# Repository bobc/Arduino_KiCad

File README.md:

# Arduino projects converted to KiCad

This repository contains Eagle projects that have been automatically converted to KiCad (v4) format  by eakit.

The conversion is as far as possible identical to the original, but some features of Eagle cannot be converted directly to KiCad. 

They may (probably will) contain conversion errors - use at own risk!

If you find a conversion problem, please raise an issue here. In case of doubt, the Eagle project should be preferred. 

If you find a problem with the design of a project, or wish to make a feature request,
please do not raise an issue here, contact the original designers.

## Copyright

Copyrights and license terms for each project are as specified by original author(s). 

## Trademarks

Please respect trademarks where applicable, and do not use without permission. 

- "Arduino", "Genuino", and the Arduino logo are trademarks of Arduino AG. https://www.arduino.cc/en/Main/CopyrightNotice

## eakit

eakit project: https://github.com/bobc/eakit

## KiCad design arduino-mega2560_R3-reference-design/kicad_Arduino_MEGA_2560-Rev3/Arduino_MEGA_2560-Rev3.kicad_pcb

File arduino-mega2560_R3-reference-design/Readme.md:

# Project automatically converted by eakit

This project was automatically converted by eakit to KiCad format.

It may (probably will) contain conversion errors - use at own risk!

eakit project: https://github.com/bobc/eakit

## Source of project

https://www.arduino.cc/en/Main/ArduinoBoardMega2560 retrieved on 2017-04-15

## License

https://www.arduino.cc/en/Main/FAQ retrieved on 2017-04-15              

> These files are licensed under a Creative Commons Attribution Share-Alike license, which allows for both personal and commercial derivative works, as long as they credit Arduino and release their designs under the same license.

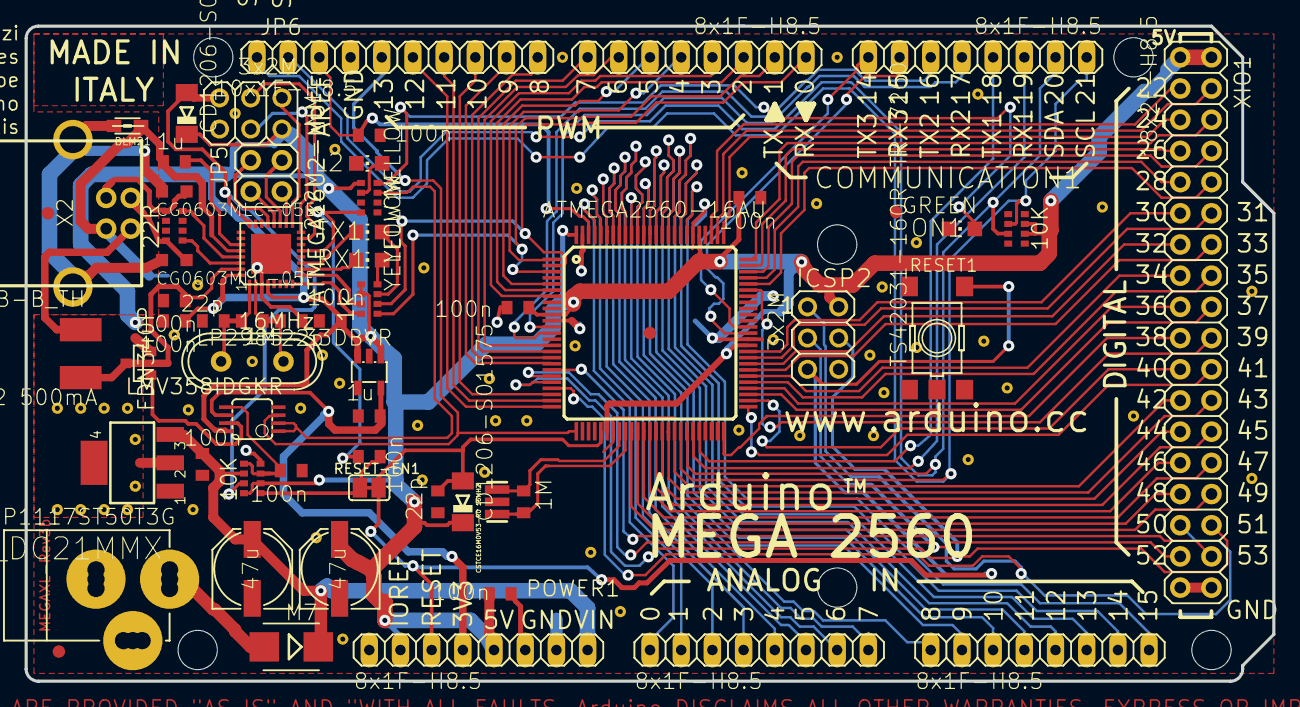
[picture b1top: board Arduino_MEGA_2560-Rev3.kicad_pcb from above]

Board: 2 copper layers, 101.6 x 53.3 mm, 123 parts (0 on the bottom side), 110 nets.

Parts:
@HOLE1: @HOLE1
@HOLE2: @HOLE2
@HOLE3: @HOLE3
@HOLE4: @HOLE4
@HOLE5: @HOLE5
@HOLE6: @HOLE6
@V1: @V1
@V2: @V2
@V3: @V3
@V4: @V4
@V5: @V5
@V6: @V6
@V7: @V7
@V8: @V8
@V9: @V9
@V10: @V10
@V11: @V11
@V12: @V12
@V13: @V13
@V14: @V14
@V15: @V15
@V16: @V16
@V17: @V17
@V18: @V18
@V19: @V19
@V20: @V20
@V21: @V21
@V22: @V22
@V23: @V23
@V24: @V24
@V25: @V25
@V26: @V26
@V27: @V27
@V28: @V28
@V29: @V29
@V30: @V30
@V31: @V31
@V32: @V32
@V33: @V33
@V34: @V34
@V35: @V35
@V36: @V36
@V37: @V37
@V38: @V38
@V39: @V39
@V40: @V40
@V41: @V41
@V42: @V42
@V43: @V43
@V44: @V44
@V45: @V45
@V46: @V46
@V47: @V47
@V48: @V48
@V49: @V49
@V50: @V50
@V51: @V51
@V52: @V52
@V53: @V53
@V54: @V54
ADCH1: 8x1F-H8.5; 1X08
ADCL1: 8x1F-H8.5; 1X08
C1, C14, C15: 22p; C0603-ROUND
C2, C3, C4, C5, C6, C7, C8, C9, C11, C12: 100n; C0603-ROUND
C10, C13: 1u; C0603-ROUND
COMMUNICATION1: 8x1F-H8.5; 1X08
D1: M7; SMB
D2, D3: CD1206-S01575; MINIMELF
F1: MF-MSMF050-2 500mA; L1812
FD1, FD2, FD3, FD4: FIDUCIALMOUNT; FIDUCIA-MOUNT
GROUND1: SJ
IC1: NCP1117ST50T3G; SOT223
IC3: ATMEGA2560-16AU; TQFP100
IC4: ATMEGA16U2-MU; MLF32
IC6: LP2985-33DBVR; SOT23-DBV
IC7: LMV358IDGKR; MSOP08
ICSP1, ICSP2: 3x2M; 2X03
JP5: 2x2M - NM; 2X02
JP6: 10x1F-H8.5; 1X10
L1: BLM21; 0805
L2: YELLOW; CHIP-LED0805
ON1: GREEN; CHIP-LED0805
PC1, PC2: 47u; PANASONIC_D
POWER1: 8x1F-H8.5; 1X08
PWML1: 8x1F-H8.5; 1X08
R1, R2: 1M; R0603-ROUND
RESET1: TS42031-160R-TR-7260; TS42
RESET-EN1: SJ
RN1, RN5: 10K; CAT16
RN2: 22R; CAY16
RN3, RN4: 1k; CAY16
RX1: YELLOW; CHIP-LED0805
T1: FDN340P; SOT-23
TX1: YELLOW; CHIP-LED0805
U$1: DISCLAIMER
X1: POWERSUPPLY_DC21MMX; POWERSUPPLY_DC-21MM
X2: USB-B_TH; PN61729
XIO1: 18x2F-H8.5; 2X18
Y1: CSTCE16M0V53-R0 16MHZ; RESONATOR
Y2: 16MHz; QS
Z1, Z2: CG0603MLC-05E; CT_CN0603

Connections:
8PB4: IC4.18, JP5.1
8PB5: IC4.19, JP5.3
8PB6: IC4.20, JP5.2
8PB7: IC4.21, JP5.4
+3V3: C13.2, IC6.5, IC7.6, POWER1.4
+5V: C4.1, C5.1, C6.1, C9.1, C11.2, D2.C, D3.C, IC1.2, IC1.4, IC3.10, IC3.31, IC3.61, IC3.80, IC3.100, IC4.4, IC4.32, IC6.1, IC6.3, IC7.8, ICSP1.2, ICSP2.2, PC2.+, POWER1.2, POWER1.5, RN1.6, RN1.7, RN3.1, RN4.5, RN4.6, RN5.2, RN5.8, T1.2, XIO1.1, XIO1.2
ADC0: ADCL1.1, IC3.97
ADC1: ADCL1.2, IC3.96
ADC2: ADCL1.3, IC3.95
ADC3: ADCL1.4, IC3.94
ADC4: ADCL1.5, IC3.93
ADC5: ADCL1.6, IC3.92
ADC6: ADCL1.7, IC3.91
ADC7: ADCL1.8, IC3.90
ADC8: ADCH1.1, IC3.89
ADC9: ADCH1.2, IC3.88
ADC10: ADCH1.3, IC3.87
ADC11: ADCH1.4, IC3.86
ADC12: ADCH1.5, IC3.85
ADC13: ADCH1.6, IC3.84
ADC14: ADCH1.7, IC3.83
ADC15: ADCH1.8, IC3.82
AREF: C3.1, IC3.98, JP6.3
CMP: C12.2, IC7.5, RN5.3, RN5.5
D+: RN2.5, X2.3, Z2.2
D-: RN2.8, X2.2, Z1.2
DTR: C7.1, IC4.13, RN3.4
GATE_CMD: IC7.7, T1.3
GND: C1.2, C2.2, C3.2, C4.2, C5.2, C6.2, C8.2, C9.2, C11.1, C12.1, C13.1, C14.2, C15.2, GROUND1.2, IC1.1, IC3.11, IC3.32, IC3.62, IC3.81, IC3.99, IC4.3, IC4.33, IC6.2, IC7.4, ICSP1.6, ICSP2.6, JP6.4, L2.C, ON1.C, PC1.-, PC2.-, POWER1.6, POWER1.7, RESET1.1, RESET1.2, RN3.5, RN5.4, X1.1, X1.3, XIO1.35, XIO1.36, Y1.2
L13: IC7.1, IC7.2, RN3.7
M8RXD: IC4.9, RN4.7
M8TXD: IC4.8, RN4.8
MISO2: IC4.17, ICSP1.1
MOSI2: IC4.16, ICSP1.4
unnamed: L2.A, RN3.2
unnamed: ON1.A, RN3.8
unnamed: RN4.4, RX1.A
unnamed: RN4.3, TX1.A
PA0: IC3.78, XIO1.3
PA1: IC3.77, XIO1.4
PA2: IC3.76, XIO1.5
PA3: IC3.75, XIO1.6
PA4: IC3.74, XIO1.7
PA5: IC3.73, XIO1.8
PA6: IC3.72, XIO1.9
PA7: IC3.71, XIO1.10
PB0: IC3.19, XIO1.34
PB1: IC3.20, ICSP2.3, XIO1.33
PB2: IC3.21, ICSP2.4, XIO1.32
PB3: IC3.22, ICSP2.1, XIO1.31
PB4: IC3.23, JP6.8
PB5: IC3.24, JP6.7
PB6: IC3.25, JP6.6
PB7: IC3.26, IC7.3, JP6.5
PC0: IC3.53, XIO1.18
PC1: IC3.54, XIO1.17
PC2: IC3.55, XIO1.16
PC3: IC3.56, XIO1.15
PC4: IC3.57, XIO1.14
PC5: IC3.58, XIO1.13
PC6: IC3.59, XIO1.12
PC7: IC3.60, XIO1.11
PD7: IC3.50, XIO1.19
PE0: IC3.2, PWML1.1, RN4.2
PE1: IC3.3, PWML1.2, RN4.1
PE3: IC3.5, PWML1.6
PE4: IC3.6, PWML1.3
PE5: IC3.7, PWML1.4
PG0: IC3.51, XIO1.22
PG1: IC3.52, XIO1.21
PG2: IC3.70, XIO1.20
PG5: IC3.1, PWML1.5
PH3: IC3.15, PWML1.7
PH4: IC3.16, PWML1.8
PH5: IC3.17, JP6.10
PH6: IC3.18, JP6.9
PL0: IC3.35, XIO1.30
PL1: IC3.36, XIO1.29
PL2: IC3.37, XIO1.28
PL3: IC3.38, XIO1.27
PL4: IC3.39, XIO1.26
PL5: IC3.40, XIO1.25
PL6: IC3.41, XIO1.24
PL7: IC3.42, XIO1.23
PWRIN: D1.A, X1.2
RD+: IC4.29, RN2.4
RD-: IC4.30, RN2.1
RESET: C1.1, C7.2, D3.A, IC3.30, ICSP2.5, POWER1.3, RESET1.3, RESET1.4, RESET-EN1.1, RESET-EN1.2, RN5.1
RESET2: D2.A, IC4.24, ICSP1.5, RN5.7
RXD1: COMMUNICATION1.3, IC3.45
RXD2: COMMUNICATION1.5, IC3.12
RXD3: COMMUNICATION1.7, IC3.63
RXL: IC4.10, RX1.C
SCK2: IC4.15, ICSP1.3
SCL: COMMUNICATION1.1, IC3.43, JP6.1, RN1.2
SDA: COMMUNICATION1.2, IC3.44, JP6.2, RN1.3
TXD1: COMMUNICATION1.4, IC3.46
TXD2: COMMUNICATION1.6, IC3.13
TXD3: COMMUNICATION1.8, IC3.64
TXL: IC4.11, TX1.C
UGND: C10.2, GROUND1.1, IC4.28, L1.1, X2.4
USBVCC: C8.1, F1.1, IC4.31, T1.1
USHIELD: L1.2, X2.P$1, X2.P$2, Z1.1, Z2.1
VIN: C2.1, D1.C, IC1.3, PC1.+, POWER1.8, RN5.6
VUCAP: C10.1, IC4.27
XT1: C14.1, IC4.1, R2.1, Y2.2
XT2: C15.1, IC4.2, R2.2, Y2.1
XTAL1: IC3.34, R1.1, Y1.3
XTAL2: IC3.33, R1.2, Y1.1
XVCC: F1.2, X2.1

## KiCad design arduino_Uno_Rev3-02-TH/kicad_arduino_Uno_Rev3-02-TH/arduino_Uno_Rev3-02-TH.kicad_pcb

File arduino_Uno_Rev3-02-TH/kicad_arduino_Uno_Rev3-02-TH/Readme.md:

# Project automatically converted by eakit

This project was automatically converted by eakit to KiCad format

It may (probably will) contain conversion errors - use at own risk!

eakit project: https://github.com/bobc/eakit

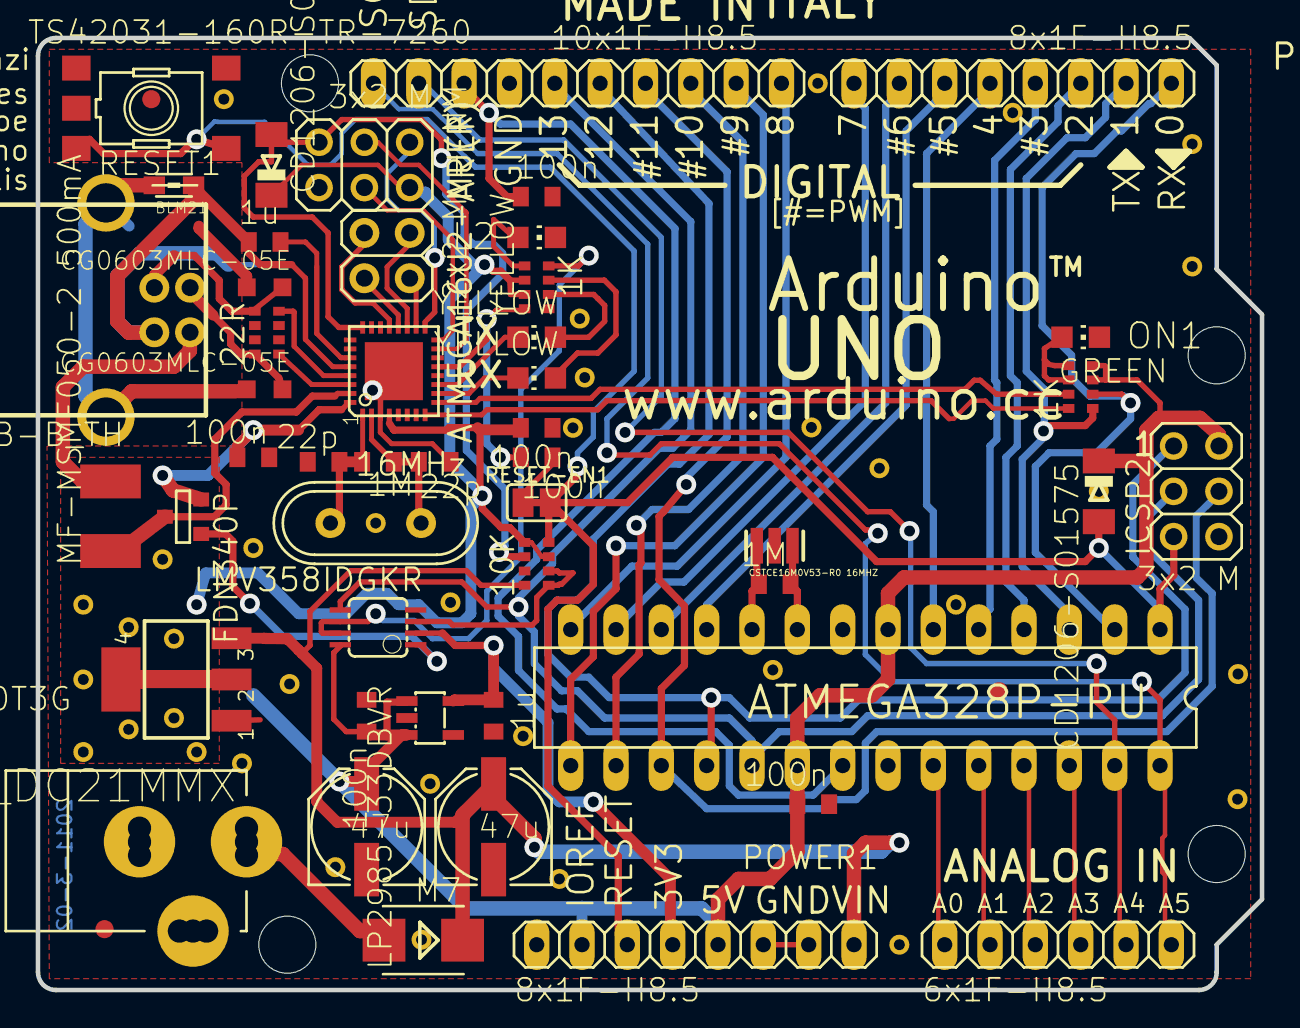
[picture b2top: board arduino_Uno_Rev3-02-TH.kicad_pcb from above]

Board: 2 copper layers, 68.6 x 53.3 mm, 92 parts (0 on the bottom side), 60 nets.

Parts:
@HOLE1: @HOLE1
@HOLE2: @HOLE2
@HOLE3: @HOLE3
@HOLE4: @HOLE4
@V1: @V1
@V2: @V2
@V3: @V3
@V4: @V4
@V5: @V5
@V6: @V6
@V7: @V7
@V8: @V8
@V9: @V9
@V10: @V10
@V11: @V11
@V12: @V12
@V13: @V13
@V14: @V14
@V15: @V15
@V16: @V16
@V17: @V17
@V18: @V18
@V19: @V19
@V20: @V20
@V21: @V21
@V22: @V22
@V23: @V23
@V24: @V24
@V25: @V25
@V26: @V26
@V27: @V27
@V28: @V28
@V29: @V29
@V30: @V30
@V31: @V31
@V32: @V32
@V33: @V33
@V34: @V34
@V35: @V35
AD1: 6x1F-H8.5; 1X06
C1, C2, C4, C5, C6, C7: 100n; C0603-ROUND
C3, C8: 1u; C0603-ROUND
C9, C11: 22p; C0603-ROUND
D1: M7; SMB
D2, D3: CD1206-S01575; MINIMELF
F1: MF-MSMF050-2 500mA; L1812
FD1, FD2, FD3: FIDUCIALMOUNT; FIDUCIA-MOUNT
GROUND1: SJ
ICSP1, ICSP2: 3x2 M; 2X03
IOH1: 10x1F-H8.5; 1X10
IOL1: 8x1F-H8.5; 1X08
JP2: 2x2 M - NM; 2X02
L1: BLM21; 0805
L2: YELLOW; CHIP-LED0805
ON1: GREEN; CHIP-LED0805
PC1, PC2: 47u; PANASONIC_D
POWER1: 8x1F-H8.5; 1X08
R1, R2: 1M; R0603-ROUND
RESET1: TS42031-160R-TR-7260; TS42
RESET-EN1: SJ
RN1: 10K; CAY16
RN2, RN4: 1K; CAY16
RN3: 22R; CAY16
RX1: YELLOW; CHIP-LED0805
T1: FDN340P; SOT-23
TX1: YELLOW; CHIP-LED0805
U1: NCP1117ST50T3G; SOT223
U2: LP2985-33DBVR; SOT23-DBV
U3: ATMEGA16U2-MU(R); MLF32
U5: LMV358IDGKR; MSOP08
U$1: DISCLAIMER
X1: POWERSUPPLY_DC21MMX; POWERSUPPLY_DC-21MM
X2: USB-B_TH; PN61729
Y1: 16MHz; QS
Y2: CSTCE16M0V53-R0 16MHZ; RESONATOR
Z1, Z2: CG0603MLC-05E; CT_CN0603
ZU4: ATMEGA328P-PU; DIL28-3

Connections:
+3V3: C3.2, POWER1.4, U2.5, U5.2
+5V: C1.2, C2.2, C6.2, C7.1, D2.C, D3.C, ICSP1.2, ICSP2.2, PC2.+, POWER1.2, POWER1.5, RN1.3, RN1.5, RN2.2, RN2.3, RN4.3, RN4.4, T1.2, U1.2, U1.4, U2.1, U2.3, U3.4, U3.32, U5.8, ZU4.7, ZU4.20
AD0: AD1.1, ZU4.23
AD1: AD1.2, ZU4.24
AD2: AD1.3, ZU4.25
AD3: AD1.4, ZU4.26
AD4/SDA: AD1.5, IOH1.9, ZU4.27
AD5/SCL: AD1.6, IOH1.10, ZU4.28
AREF: C4.2, IOH1.8, ZU4.21
CMP: RN1.1, RN1.2, U5.3
D+: RN3.5, X2.3, Z1.1
D-: RN3.8, X2.2, Z2.1
DTR: C5.1, RN2.4, U3.13
GATE_CMD: T1.3, U5.1
GND: C1.1, C2.1, C3.1, C4.1, C6.1, C7.2, C9.2, C11.2, GROUND1.1, ICSP1.6, ICSP2.6, IOH1.7, L2.C, ON1.C, PC1.-, PC2.-, POWER1.6, POWER1.7, RESET1.1, RESET1.2, RN1.7, RN2.5, U1.1, U2.2, U3.3, U3.33, U5.4, X1.1, X1.3, Y2.2, ZU4.8, ZU4.22
IO0: IOL1.1, RN4.2, ZU4.2
IO1: IOL1.2, RN4.1, ZU4.3
IO2: IOL1.3, ZU4.4
IO3: IOL1.4, ZU4.5
IO4: IOL1.5, ZU4.6
IO5: IOL1.6, ZU4.11
IO6: IOL1.7, ZU4.12
IO7: IOL1.8, ZU4.13
IO8: IOH1.1, ZU4.14
IO9: IOH1.2, ZU4.15
L13: RN2.8, U5.6, U5.7
M8RXD: RN4.7, U3.9
M8TXD: RN4.8, U3.8
MISO: ICSP2.1, IOH1.5, ZU4.18
MISO2: ICSP1.1, U3.17
MOSI: ICSP2.4, IOH1.4, ZU4.17
MOSI2: ICSP1.4, U3.16
unnamed: L2.A, RN2.1
unnamed: ON1.A, RN4.5, RN4.6
unnamed: RN2.7, RX1.A
unnamed: RN2.6, TX1.A
PB4: JP2.1, U3.18
PB5: JP2.3, U3.19
PB6: JP2.2, U3.20
PB7: JP2.4, U3.21
PWRIN: D1.A, X1.2
RD+: RN3.4, U3.29
RD-: RN3.1, U3.30
RESET: C5.2, D2.A, ICSP2.5, POWER1.3, RESET1.3, RESET1.4, RESET-EN1.1, RESET-EN1.2, RN1.4, ZU4.1
RESET2: D3.A, ICSP1.5, RN1.6, U3.24
RXLED: RX1.C, U3.10
SCK: ICSP2.3, IOH1.6, U5.5, ZU4.19
SCK2: ICSP1.3, U3.15
SS: IOH1.3, ZU4.16
TP_VUCAP: C8.1, U3.27
TXLED: TX1.C, U3.11
UGND: C8.2, GROUND1.2, L1.1, U3.28, X2.4
USBVCC: F1.1, T1.1, U3.31
USHIELD: L1.2, X2.P$1, X2.P$2, Z1.2, Z2.2
VIN: D1.C, PC1.+, POWER1.8, RN1.8, U1.3
XT1: C9.1, R1.1, U3.1, Y1.2
XT2: C11.1, R1.2, U3.2, Y1.1
XTAL1: R2.1, Y2.3, ZU4.9
XTAL2: R2.2, Y2.1, ZU4.10
XUSB: F1.2, X2.1

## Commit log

2017-04-16 Conversion of Uno project
2017-04-16 Conversion of Mega_2560-Rev3
